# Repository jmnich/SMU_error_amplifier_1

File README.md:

# SMU_error_amplifier_1

Error amplifier module for HTBlog Source Measure Unit

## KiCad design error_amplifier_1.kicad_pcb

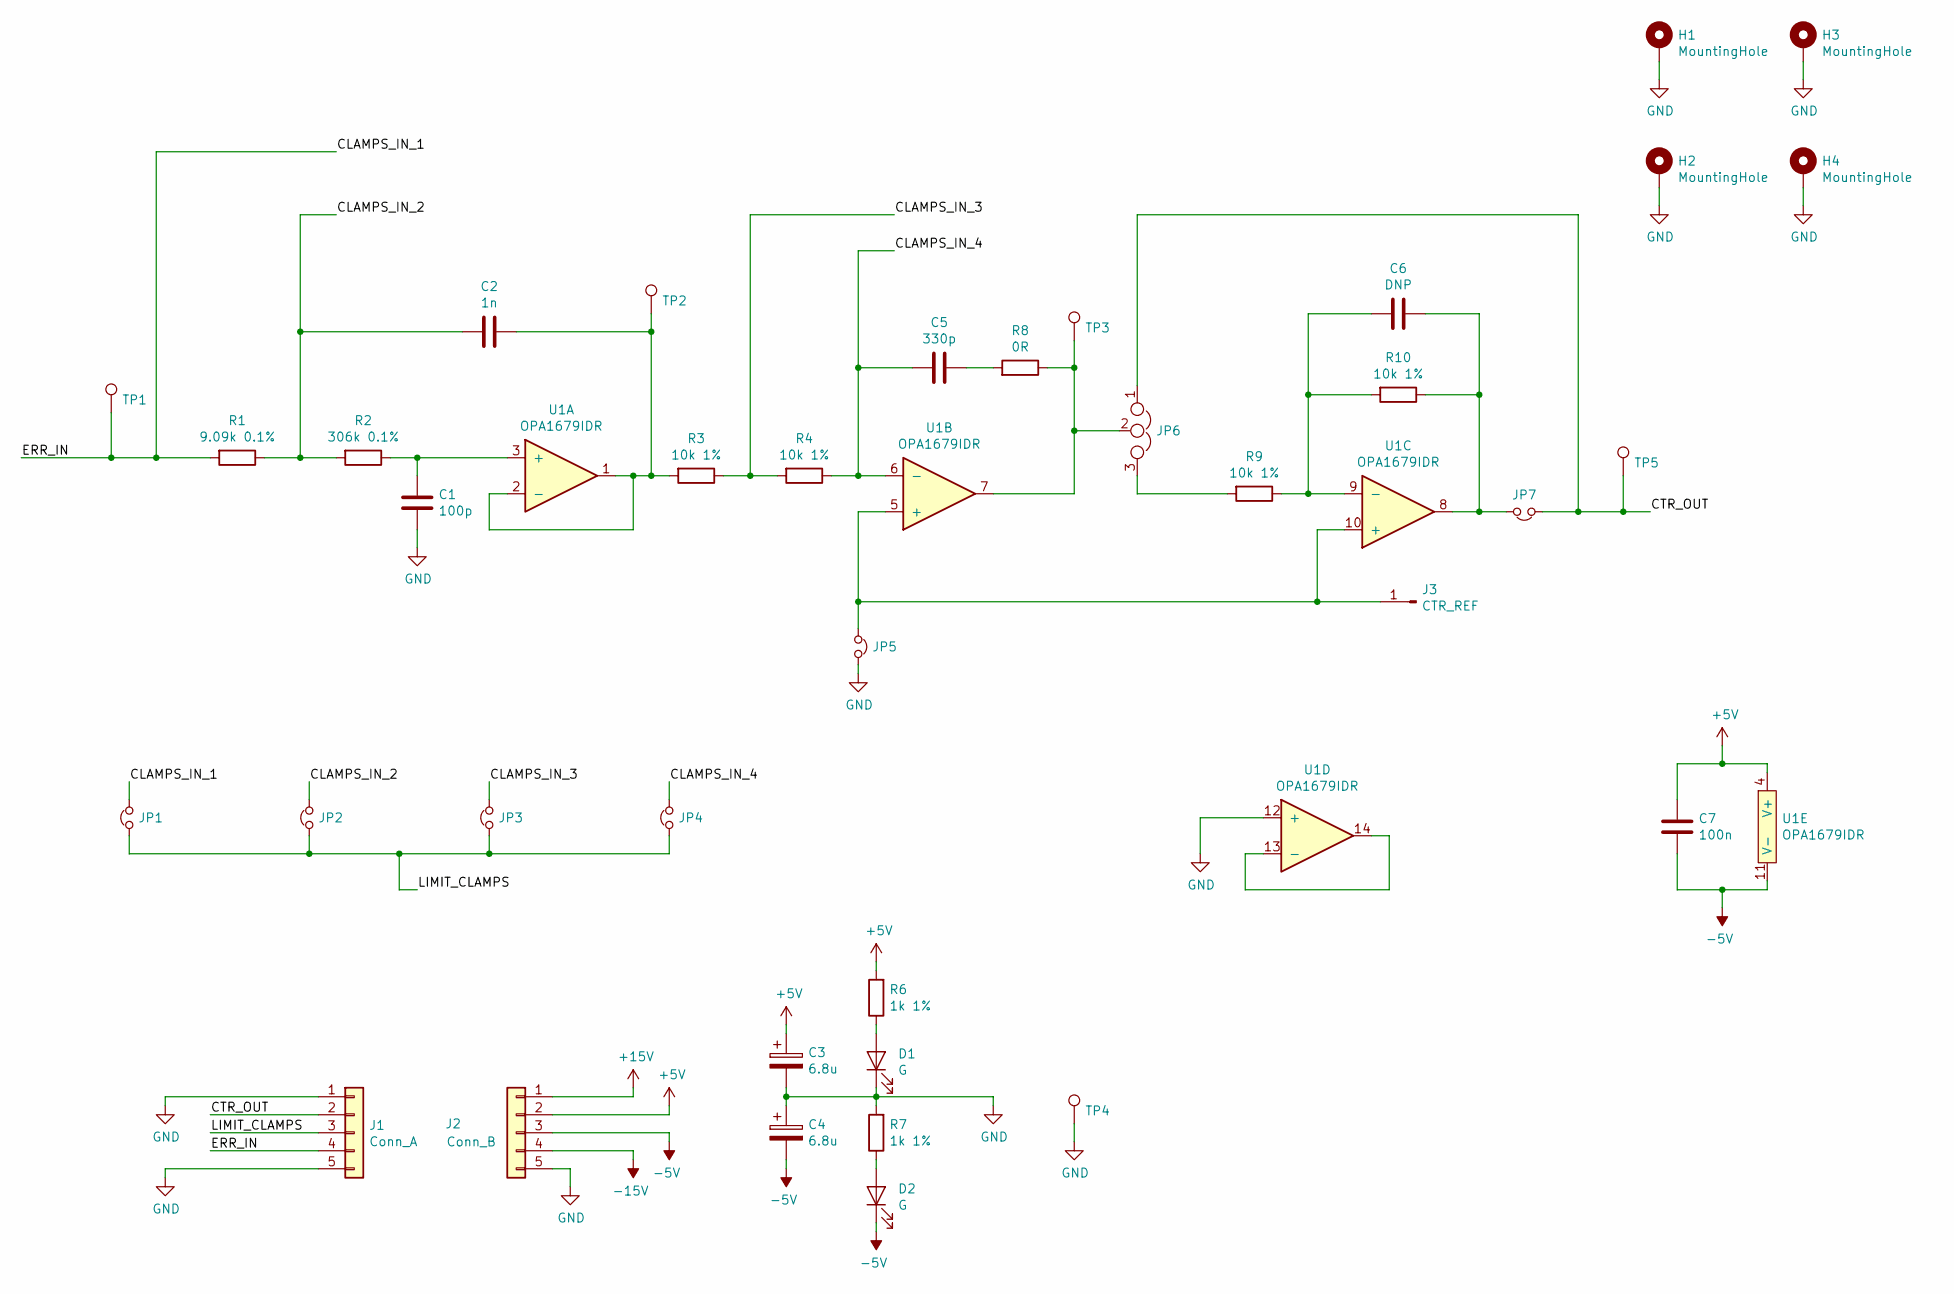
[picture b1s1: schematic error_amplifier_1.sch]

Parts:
C1: 100p; C_0603_1608Metric_Pad1.05x0.95mm_HandSolder
C2: 1n; C_0603_1608Metric_Pad1.05x0.95mm_HandSolder
C3, C4: 6.8u; CP_Elec_6.3x5.9
C5: 330p; C_0603_1608Metric_Pad1.05x0.95mm_HandSolder
C6: DNP; C_0603_1608Metric_Pad1.05x0.95mm_HandSolder
C7: 100n; C_0603_1608Metric_Pad1.05x0.95mm_HandSolder
D1, D2: G; LED_0603_1608Metric_Pad1.05x0.95mm_HandSolder
H1, H2, H3, H4: MountingHole; MountingHole_3.2mm_M3_Pad_Via
J1: Conn_A; PinSocket_1x05_P2.54mm_Vertical
J2: Conn_B; PinSocket_1x05_P2.54mm_Vertical
J3: CTR_REF; MountingHole_2.2mm_M2_Pad_Via
JP1, JP2, JP3, JP4, JP7: Jumper_NC_Small; SolderJumper-2_P1.3mm_Open_RoundedPad1.0x1.5mm
JP5: Jumper_NC_Small; SolderJumper-2_P1.3mm_Bridged_RoundedPad1.0x1.5mm
JP6: Jumper_NC_Dual; SolderJumper-3_P1.3mm_Bridged12_RoundedPad1.0x1.5mm_NumberL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
R1: 9.09k 0.1%; R_0603_1608Metric_Pad1.05x0.95mm_HandSolder
R2: 306k 0.1%; R_0603_1608Metric_Pad1.05x0.95mm_HandSolder
R3, R4, R9, R10: 10k 1%; R_0603_1608Metric_Pad1.05x0.95mm_HandSolder
R6, R7: 1k 1%; R_0603_1608Metric_Pad1.05x0.95mm_HandSolder
R8: 0R; R_0603_1608Metric_Pad1.05x0.95mm_HandSolder
TP1, TP2, TP3, TP5: TestPoint; TestPoint_Pad_D2.0mm
TP4: TestPoint; TestPoint_Keystone_5010-5014_Multipurpose
U1: OPA1679IDR; SOIC-14_3.9x8.7mm_P1.27mm

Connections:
+5V: C3.1, C7.2, J2.2, R6.2, U1.4 (V+)
+15V: J2.1
-5V: C4.2, C7.1, D2.1 (K), J2.3, U1.11 (V-)
-15V: J2.4
/CLAMPS_IN_1: J1.4, JP1.2, R1.2, TP1.1
/CLAMPS_IN_2: C2.2, JP2.2, R1.1, R2.2
/CLAMPS_IN_3: JP3.2, R3.1, R4.2
/CLAMPS_IN_4: C5.2, JP4.2, R4.1, U1.6 (-)
/CTR_OUT: J1.2, JP6.1, JP7.1, TP5.1
/LIMIT_CLAMPS: J1.3, JP1.1, JP2.1, JP3.1, JP4.1
GND: C1.2, C3.2, C4.1, D1.1 (K), H1.1, H2.1, H3.1, H4.1, J1.1, J1.5, J2.5, JP5.2, R7.2, TP4.1, U1.12 (+)
unnamed: C1.1, R2.1, U1.3 (+)
unnamed: C2.1, R3.2, TP2.1, U1.1, U1.2 (-)
unnamed: C5.1, R8.2
unnamed: C6.1, JP7.2, R10.1, U1.8
unnamed: C6.2, R9.1, R10.2, U1.9 (-)
unnamed: D1.2 (A), R6.1
unnamed: D2.2 (A), R7.1
unnamed: J3.1, JP5.1, U1.5 (+), U1.10 (+)
unnamed: JP6.2, R8.1, TP3.1, U1.7
unnamed: JP6.3, R9.2
unnamed: U1.13 (-), U1.14

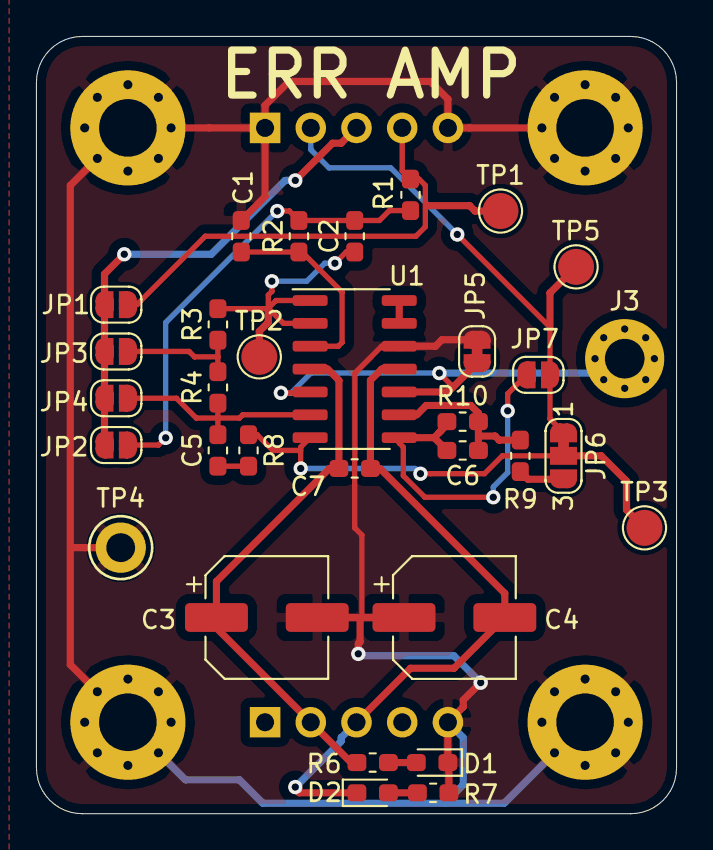
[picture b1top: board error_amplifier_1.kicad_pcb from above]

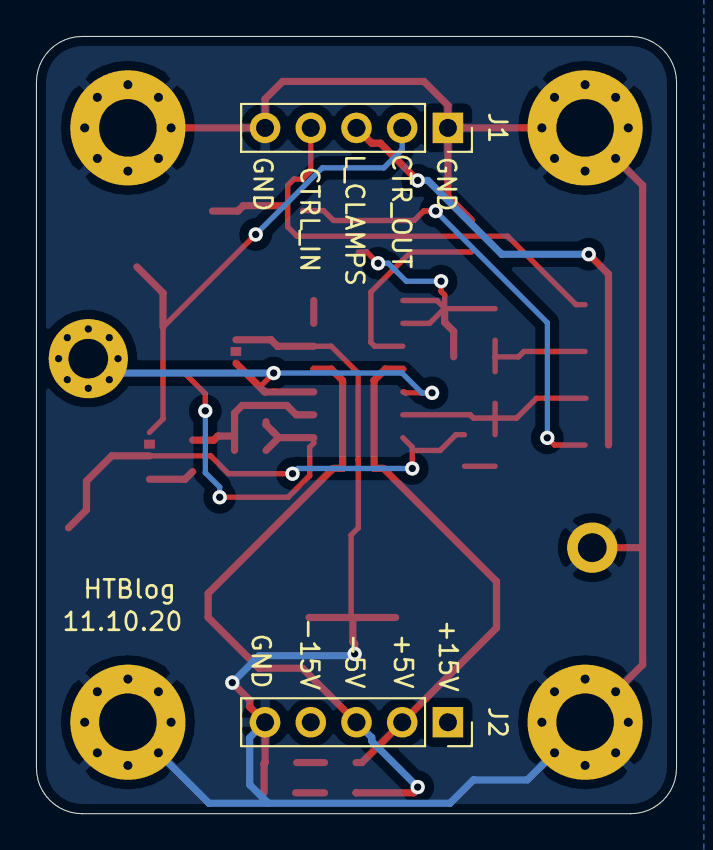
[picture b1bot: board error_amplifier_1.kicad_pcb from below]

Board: 2 copper layers, 35.6 x 43.2 mm, 38 parts (2 on the bottom side), 20 nets.

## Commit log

2020-10-17 added image
2020-10-17 readme
2020-10-27 production files
